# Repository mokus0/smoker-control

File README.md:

Smoker Command Center
======================

First, an up front warning:  I don't have nearly enough time for this project.  Feel free to use anything you want from this project, and if you run into issues I'd love to try to help - *if* I can find the time.  And that's a BIG "if".

Now that that's out of the way... This is the very beginning of a project that brings together two of my favorite hobbies, neither of which I do nearly enough of: electronics and cooking.  There's not much to see here yet, and there may never be, but what I'd *like* to make here is a weatherproof, wireless, battery powered (with solar charging) general-purpose sensor pod, rigged up with a bunch of useful sensors on my backyard smoker.

On the software side, I'd like to put together a sort of "big board", giving me a nice overview of the recent history of the sensors and some analysis of the data (rates of change of temperatures, estimated amount of fuel to add, estimated time to reach target temperatures, etc.).

For now, I've got a sensor measurement board design I'm working on.  It's primarily designed for precision resistance measurements across 5 decades, but useful for a lot of other analog sensors.

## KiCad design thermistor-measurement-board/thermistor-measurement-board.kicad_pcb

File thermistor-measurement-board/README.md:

Sensor front-end board
=======================

This board is an analog front-end designed to be able to interface with a very wide variety of sensors.  The immediate application is to read thermistors and RTDs, but it is massively overengineered for the task so it can be easily adapted to many other sensors.

The board provides 16 single-ended channels (or, depending how the board is stuffed, these 16 channels can be paired in any combination for differential measurement).  I haven't built the board yet but each input *should* have very high input impedance (around 2 GΩ on the high gain channel and 10 TΩ on the unity-gain channel), very low noise, very good linearity and (after ADC calibration) very good overall accuracy.  Up to 2 channels can be sampled simultaneously by a 24-bit ADC with programmable gain from 1 to 32 V/V, and the input amps are additionally configured for two different levels of gain (unity and 100x) to widen the range the board can handle.

Each channel can also be independently connected to one of two bias supplies, with very accurate on-board voltage and current references.

Pretty much every major component on the board other than the muxes is optional and can be bypassed to use the rest of the board in a useful way.

We shall see how the analog performance comes out; I've been working in a very limited space to keep prototyping costs down, but I've also been pretty careful with the layout so I'm optimistic.  I've managed to fit it on a 1.2" by 2" board using relatively large components (nothing smaller than 0402) so it should still be feasible to hand-assemble.  I've tried to keep things reasonably accessible for rework as well, but in some areas rework will be a challenge without very good tools.

Contents
=========

(most parts optional, see schematic for details): 

* MAX6070 voltage reference (x2)

* AD8277 dual difference amp and AD8607 dual op amp configured as two current sources (limited to relatively low output currents, intended for use as bias supplies for resistive sensors)

* MAX14661 multiplexer (x2): the first connects 2 power sources to 16 sensor channels and the other connects the same sensor channels to 2 sampling channels.  These are on separate pins to support 3-terminal measurements, and with a bit of finagling channels can be ganged together to support 4-terminal measurements.

* MAX4209 and MCP6N11 instrument amps to provide high impedance at the sensor measurement terminals and a couple gain ranges.

* MCP3911 24-bit ADC with analog front-end.  This is a very inexpensive part so I'm a bit concerned it may not perform as advertised, but I thought I'd give it a try.  On paper it's an interesting design, achieving very impressive specs for its price point through DSP techniques.

All parts except the current source have reasonably low active mode power consumption and very low power shutdown modes.  Current sources will pull around 250 µA each, but in practice I expect that for a full shutdown I'll cut power to the whole board.

Power supply info
==================

* MAX6070AAUT12+T (x2)

    Voltage:            2.7V - 5.5V (6V absolute max)
    
    Active current:     130 µA typical, 200 µA max
    
    Shutdown current:   6 µA max

* AD8277

    Voltage:            ±2V - ±18V (single or dual supply)
    
    Active current:     200 µA max (per channel?)
    
    Shutdown current:   N/A

* AD8607

    Voltage:            1.8V - 5V (6V absolute max)
    
    Active current:     40 µA typical, 50 µA max (per channel, x2)
    
    Shutdown current:   N/A

* MAX14661(x2)

    Voltage:            1.6V - 5.5V (6V absolute max)
    
    Active current:     675 µA typical, 1500 µA max
    
    Shutdown current:   1 µA max.

* MAX4209

    Voltage:            2.85V - 5.5V (6V absolute max)
    
    Active current:     1.4 mA typical, 2.3 mA max (using REFIN buffer)
    
    Shutdown current:   1.4 µA typical, 5 µA max.
    
    REFIN divider cur:  0.4 µA

* MCP6N11

    Voltage:            1.8V - 5.5V (6.5V absolute max)
    
    Active current:     800 µA typical, 1.1 mA max
    
    Shutdown current:   ~1 µA typical
    
    REF divider cur:    0.4 µA

* MCP3911

    Voltage:            2.7V - 3.6V (4V absolute max)
    
    Active current:     1.7 - 5.1 mA typical,
                        2.4 - ~7.5 mA max
                        (depending on configuration)
    
    Shutdown current:   2 µA max.

* Overall system (excluding dividers, leakage currents, etc)

    Voltage:            2.85V - 3.6V (4V absolute max)
    
    Active current:     ~10 mA max (lowest power ADC config)
    
    Shutdown current:   527 uA max (500 uA from the current sources).

Signal parameters, error analysis, etc
=======================================

* Voltage references

    When driving current source, will likely use 1.25V version.
    
    specs here are for "A" grade
    
    Initial accuracy ± 0.04%, max 6 ppm/ºC drift, 3.6 µV P-P noise (0.1 Hz to 10 kHz).
    200 mV dropout.
    Settling time after power-up or enable: 6 ms (or 60 µs if filter cap C208/C210 is removed)
    Very low output impedance (~ 0.1 Ω typically at 1 mA)

* Current sources

    These work by using a unity-gain difference amplifier to drive a set resistor (on the high side of a load) to a target voltage.  The second op-amp increases the input impedance of the feedback loop (without the op-amp, this would be 80 kΩ) to reduce error when driving high-impedance loads.
    
    Because of the feedback topology, all input voltages from GND to VS are valid as long as VS is at least 3V.  The output swing will range from GND (plus whatever offset is present at minimum load resistance) to VS - 0.2V - V_in at the low side of the sense resistor.
    
    difference amp (specs here are for "B" grade):
    
    system offset 200 µV max (0.012% with 1.25V reference)
    gain error 0.02% max (250 µV with 1.25V reference)
    differential input impedance 80 kΩ (about 1.25 ppm error on input from voltage ref's 0.1 Ω output)
    settling time to 0.001%: 16 µs max
    output noise 7 µV P-P max, 0.1 Hz - 10 kHz
    
    feedback buffer:
    
    offset error 50 µV max (0.004% with 1.25V reference)
    input bias current 1 pA max (1 µV error with 1 MΩ set resistor)
    output noise 3.5 µV P-P max, 0.1 Hz - 1 MHz
    
    total set-resistor voltage error (vref + diff amp + feedback buffer): 1 mV (0.08%).
    
    At these error levels, although the resistor error technically composes nonlinearly, the nonlinearity is negligible.  With a 0.02% set resistor, for xample, current accuracy should be 0.1% worst-case.  A 0.1% resistor should give 0.18% percent worst-case current accuracy.

* Bias mux

    This mux distributes bias current from either or both sources to any combination of the sensor channels.  The measurement is performed through a separate mux, to eliminate measurement errors due to the switch resistance of this mux.  If using a voltage-mode bias, the mux will add 8-12Ω (max) of fairly flat (24 mΩ, typically around 0.5%) source impedance, with channels typically matching to within 0.25Ω (around 5%).  Datasheet is not clear on whether these values are stable over time but I'd expect they are, and channels could be individually calibrated.
    
    input/output signal voltage range: ±5.5V
    ESD protection: ±10kV on all muxed pins
    switch on-state leakage current ±50 nA max (±5% error on 1 µA bias current).  This is with lines held at absolute limits: not sure what leakage would be at more typical voltages (≤0.6V), or how consistent it might be.  This figure definitely makes me worry about this mux.  To be fair, the graphs appear to show the "typical" figure to be a couple orders of magnitude lower, and very flat in all dimensions across ranges we care about.  I think I'm going to roll the dice on it - I have several options to work around it if it does turn out to be problematic (including the perfectly viable "screw it, let it be wrong at low bias currents" option, which won't harm my initial application for this board much).

* Sense mux

    This mux connects sensor channels to measurement channels.
    
    Same part as bias mux.

* MAX4208/9

    Not suitable for both channels; it's only designed for up to about ±100 mV differential mode.  Future iterations may use MCP6N11 for both channels as it seems well-suited to a wide gain range, but for now I want to try this one out for a high-gain channel as it has several features that make it appealing for high-gain small-signal applications.

    Input common-mode range (3V supply): -0.1V to 1.7V.  IN- will typically be GND so IN+ can swing rail-to-rail.
    Output voltage swings to within a few tens of mV of either rail.
    ADC input absolute max is only +2V though, so output channels are clamped to 1.8V by zener diodes (TODO: is there a better choice here?).  If amp tries to drive higher than 1.8V, it will source up to 20 mA (typical) through the zener diodes (and can do so continuously with no harm other than the wasted power), after which it will take about 0.5 ms to recover.
    
    Input differential mode range:
    datasheet recommends keeping below 100mV or linearity is poor.
    
    Input resistance 2 GΩ, bias current 1 pA (negligible error for 1 uA bias current)
    
    Input offset ±20 µV max
    Gain can be set for unity or higher.  Gain error at 100V/V with Vdiff ±20mV (doesn't say how accurate the set resistors were): ±0.25% max

* MCP6N11

    Input common-mode range (3V supply): -0.2V to 3.15V
    Common-mode non-linearity (non-linear change of input offset with common-mode voltage): 0.1% worst-case (unity gain, 1.8V supply) - typically much better
    Gain error ±1% max, but very low drift (6 ppm/ºC)
    Differential non-linearity
        (G = 1): ±30 ppm typical, ±500 ppm max
        (G = 10, 100): ±100 ppm typical, ±2000 ppm max
    
    Input bias current 10 pA typical, 5 nA max (at 125ºC)
    Input resistance 10TΩ
    
    Output voltage swing: within about 25 mV of rails
    Output impedance: (G = 1, 10) 900Ω typical (G = 100) 600Ω typical

* ADC

    This is a pretty interesting ADC architecture - it uses a 5-level sigma-delta frontend and DSP oversampling to achieve 24 bit resolution with fairly low noise and very good overall signal performance (if oversampling by a large enough factor).
    Biggest weakness is that it only tolerates ±2V input.
    
    Input absolute range: ±1V
    Input differential-mode range: ±0.6V full scale (divided by gain)
    Offset, gain error and vref tolerance are relatively high but can be calibrated fairly well (gain error drift is 1 ppm/ºC, INL is 5 ppm, internal vref TC is 7 ppm/ºC)

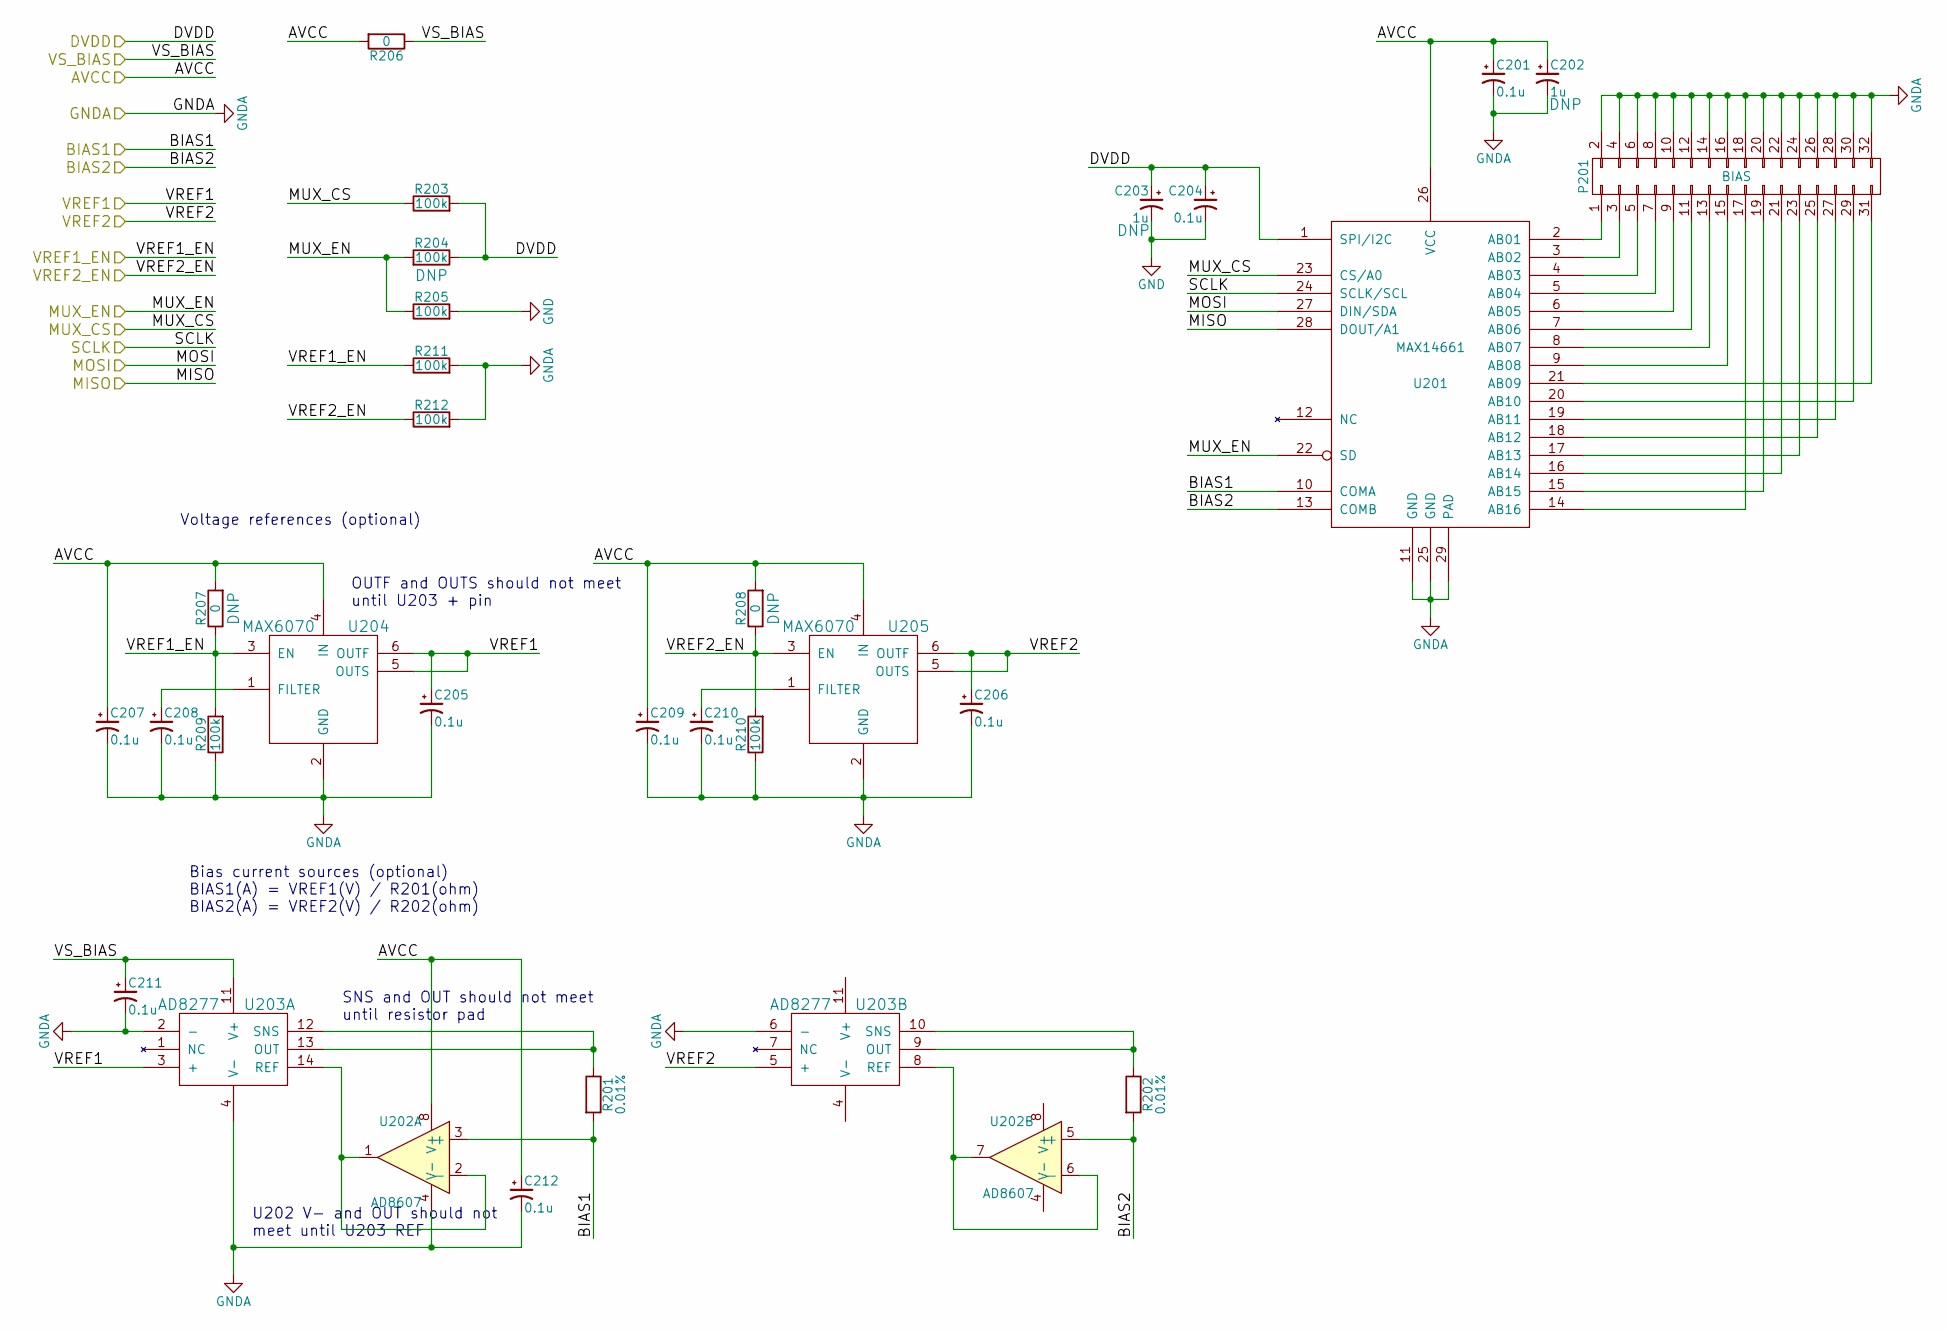
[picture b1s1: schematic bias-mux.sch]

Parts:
C201, C204, C205, C206, C207, C208, C209, C210, C211, C212: 0.1u; C_0402
C202, C203: 1u; C_0603
P201: BIAS; Pin_Header_Straight_2x16
R201, R202: 0.01%; R_0603
R203, R204, R205: 100k; R_0603
R206, R207, R208: 0; R_0402
R209, R210, R211, R212: 100k; R_0402
U201: MAX14661; Maxim_90-0035
U202: AD8607; MSOP-8_3x3mm_Pitch0.65mm
U203: AD8277; SOIC-14_3.9x8.7mm_Pitch1.27mm
U204, U205: MAX6070; Maxim_90-0175

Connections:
/ADC/AVCC: C201.1, C202.1, C207.1, C209.1, C212.1, R206.2, R207.2, R208.2, U201.26 (VCC), U202.8 (V+), U204.4 (IN), U205.4 (IN); also elsewhere on the board
/ADC/DVDD: C203.1, C204.1, R203.2, R204.1, U201.1 (SPI/I2C); also elsewhere on the board
/ADC/MISO: U201.28 (DOUT/A1); also elsewhere on the board
/ADC/MOSI: U201.27 (DIN/SDA); also elsewhere on the board
/ADC/SCLK: U201.24 (SCLK/SCL); also elsewhere on the board
/Bias/BIAS1: R201.2, U201.10 (COMA), U202.3 (+); also elsewhere on the board
/Bias/BIAS2: R202.2, U201.13 (COMB), U202.5 (+); also elsewhere on the board
/Bias/MUX_CS: R203.1, U201.23 (CS/A0); also elsewhere on the board
/Bias/MUX_EN: R204.2, R205.1, U201.22 (SD); also elsewhere on the board
/Bias/VREF1: C205.1, U203.3 (+), U204.5 (OUTS), U204.6 (OUTF); also elsewhere on the board
/Bias/VREF1_EN: R207.1, R209.2, R211.1, U204.3 (EN); also elsewhere on the board
/Bias/VREF2: C206.1, U203.5 (+), U205.5 (OUTS), U205.6 (OUTF); also elsewhere on the board
/Bias/VREF2_EN: R208.1, R210.2, R212.1, U205.3 (EN); also elsewhere on the board
/Bias/VS_BIAS: C211.1, R206.1, U203.11 (V+); also elsewhere on the board
GND: C203.2, C204.2, R205.2; also elsewhere on the board
GNDA: C201.2, C202.2, C205.2, C206.2, C207.2, C208.2, C209.2, C210.2, C211.2, C212.2, P201.2, P201.4, P201.6, P201.8, P201.10, P201.12, P201.14, P201.16, P201.18, P201.20, P201.22, P201.24, P201.26, P201.28, P201.30, P201.32, R209.1, R210.1, R211.2, R212.2, U201.11 (GND), U201.25 (GND), U201.29 (PAD), U202.4 (V-), U203.2 (-), U203.4 (V-), U203.6 (-), U204.2 (GND), U205.2 (GND); also elsewhere on the board
unnamed: C208.1, U204.1 (FILTER)
unnamed: C210.1, U205.1 (FILTER)
unnamed: P201.1, U201.2 (AB01)
unnamed: P201.3, U201.3 (AB02)
unnamed: P201.5, U201.4 (AB03)
unnamed: P201.7, U201.5 (AB04)
unnamed: P201.9, U201.6 (AB05)
unnamed: P201.11, U201.7 (AB06)
unnamed: P201.13, U201.8 (AB07)
unnamed: P201.15, U201.9 (AB08)
unnamed: P201.17, U201.14 (AB16)
unnamed: P201.19, U201.15 (AB15)
unnamed: P201.21, U201.16 (AB14)
unnamed: P201.23, U201.17 (AB13)
unnamed: P201.25, U201.18 (AB12)
unnamed: P201.27, U201.19 (AB11)
unnamed: P201.29, U201.20 (AB10)
unnamed: P201.31, U201.21 (AB09)
unnamed: R201.1, U203.12 (SNS), U203.13 (OUT)
unnamed: R202.1, U203.9 (OUT), U203.10 (SNS)
unnamed: U202.1, U202.2 (-), U203.14 (REF)
unnamed: U202.6 (-), U202.7, U203.8 (REF)

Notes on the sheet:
Bias current sources (optional) BIAS1(A) = VREF1(V) / R201(ohm) BIAS2(A) = VREF2(V) / R202(ohm)
SNS and OUT should not meet until resistor pad
OUTF and OUTS should not meet until U203 + pin
Voltage references (optional)
U202 V- and OUT should not meet until U203 REF

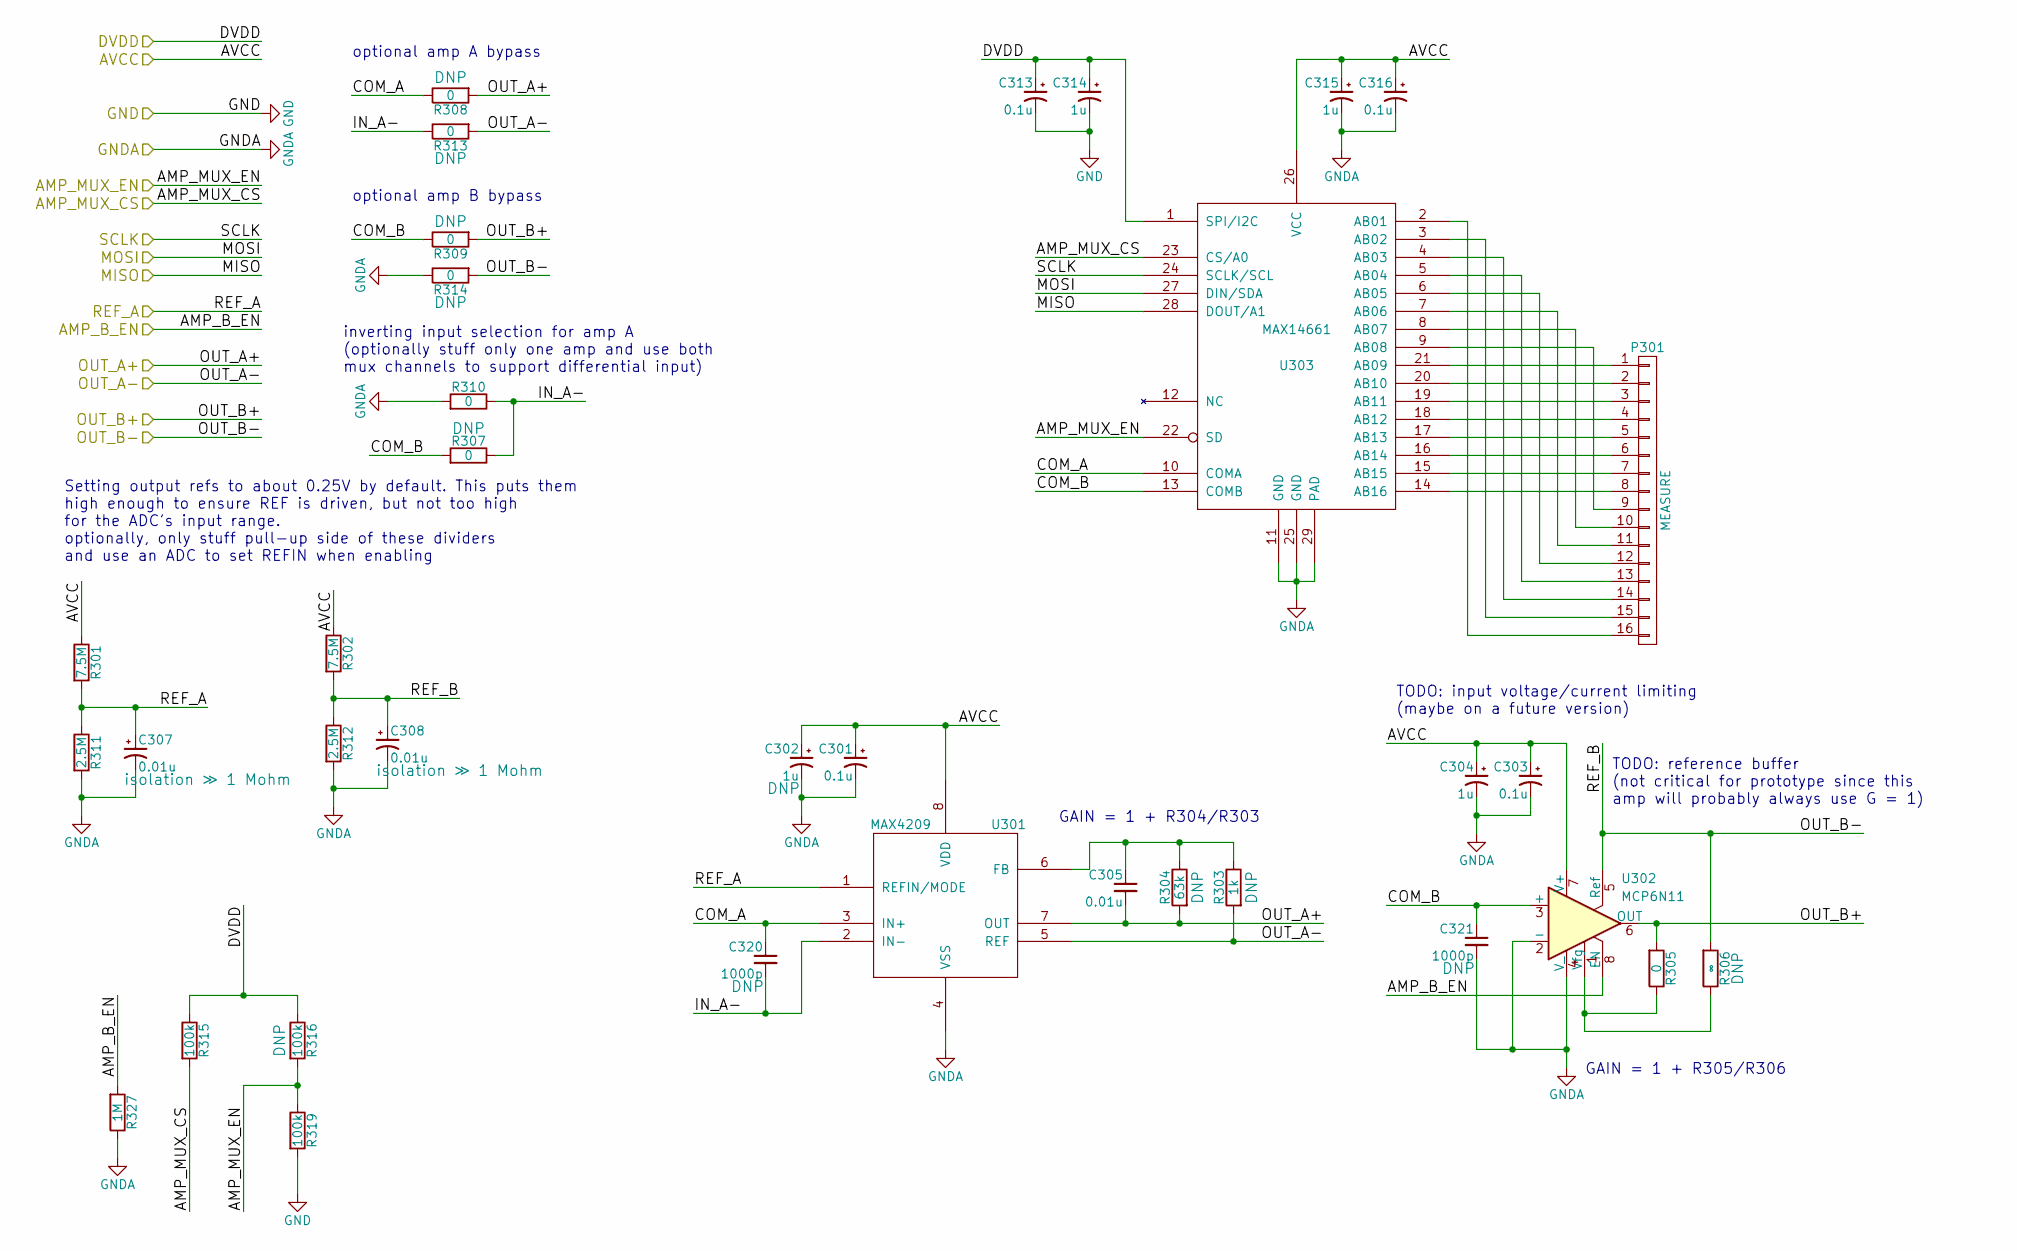
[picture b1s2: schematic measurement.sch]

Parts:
C301, C303, C313, C316: 0.1u; C_0402
C302, C304, C314, C315: 1u; C_0603
C305, C307, C308: 0.01u; C_0402
C320, C321: 1000p; C_0402
P301: MEASURE; Pin_Header_Straight_1x16
R301, R302: 7.5M; R_0402
R303: 1k; R_0402
R304: 63k; R_0402
R305, R307, R308, R310, R313: 0; R_0402
R306: ∞; R_0402
R309, R314: 0; R_0603
R311, R312: 2.5M; R_0402
R315, R316, R319: 100k; R_0603
R327: 1M; R_0603
U301: MAX4209; MSOP-8_3x3mm_Pitch0.65mm
U302: MCP6N11; SOIC-8_3.9x4.9mm_Pitch1.27mm
U303: MAX14661; Maxim_90-0035

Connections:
/ADC/AVCC: C301.1, C302.1, C303.1, C304.1, C315.1, C316.1, R301.1, R302.1, U301.8 (VDD), U302.7 (V+), U303.26 (VCC); also elsewhere on the board
/ADC/DVDD: C313.1, C314.1, R315.1, R316.1, U303.1 (SPI/I2C); also elsewhere on the board
/ADC/MISO: U303.28 (DOUT/A1); also elsewhere on the board
/ADC/MOSI: U303.27 (DIN/SDA); also elsewhere on the board
/ADC/OUT_A+: C305.2, R304.2, R308.2, U301.7 (OUT); also elsewhere on the board
/ADC/OUT_A-: R303.2, R313.2, U301.5 (REF); also elsewhere on the board
/ADC/OUT_B+: R305.2, R309.2, U302.6 (OUT); also elsewhere on the board
/ADC/OUT_B-: C308.1, R302.2, R306.2, R312.1, R314.2, U302.5 (Ref); also elsewhere on the board
/ADC/SCLK: U303.24 (SCLK/SCL); also elsewhere on the board
/Interface/AMP_MUX_CS: R315.2, U303.23 (CS/A0); also elsewhere on the board
/Interface/AMP_MUX_EN: R316.2, R319.1, U303.22 (SD); also elsewhere on the board
/Interface/REF_A: C307.1, R301.2, R311.1, U301.1 (REFIN/MODE); also elsewhere on the board
/Sensor input/AMP_B_EN: R327.2, U302.8 (EN); also elsewhere on the board
/Sensor input/COM_A: C320.1, R308.1, U301.3 (IN+), U303.10 (COMA)
/Sensor input/COM_B: C321.1, R307.2, R309.1, U302.3 (+), U303.13 (COMB)
/Sensor input/IN_A-: C320.2, R307.1, R310.1, R313.1, U301.2 (IN-)
GND: C313.2, C314.2, R319.2; also elsewhere on the board
GNDA: C301.2, C302.2, C303.2, C304.2, C307.2, C308.2, C315.2, C316.2, C321.2, R310.2, R311.2, R312.2, R314.1, R327.1, U301.4 (VSS), U302.2 (-), U302.4 (V_), U303.11 (GND), U303.25 (GND), U303.29 (PAD); also elsewhere on the board
unnamed: C305.1, R303.1, R304.1, U301.6 (FB)
unnamed: P301.1, U303.21 (AB09)
unnamed: P301.2, U303.20 (AB10)
unnamed: P301.3, U303.19 (AB11)
unnamed: P301.4, U303.18 (AB12)
unnamed: P301.5, U303.17 (AB13)
unnamed: P301.6, U303.16 (AB14)
unnamed: P301.7, U303.15 (AB15)
unnamed: P301.8, U303.14 (AB16)
unnamed: P301.9, U303.9 (AB08)
unnamed: P301.10, U303.8 (AB07)
unnamed: P301.11, U303.7 (AB06)
unnamed: P301.12, U303.6 (AB05)
unnamed: P301.13, U303.5 (AB04)
unnamed: P301.14, U303.4 (AB03)
unnamed: P301.15, U303.3 (AB02)
unnamed: P301.16, U303.2 (AB01)
unnamed: R305.1, R306.1, U302.1 (Vfg)

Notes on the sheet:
optional amp A bypass
GAIN = 1 + R304/R303
inverting input selection for amp A (optionally stuff only one amp and use both mux channels to support differential input)
Setting output refs to about 0.25V by default. This puts them high enough to ensure REF is driven, but not too high for the ADC's input range. optionally, only stuff pull-up side of these dividers and use an ADC to set REFIN when enabling
TODO: reference buffer (not critical for prototype since this amp will probably always use G = 1)
GAIN = 1 + R305/R306
optional amp B bypass
TODO: input voltage/current limiting (maybe on a future version)

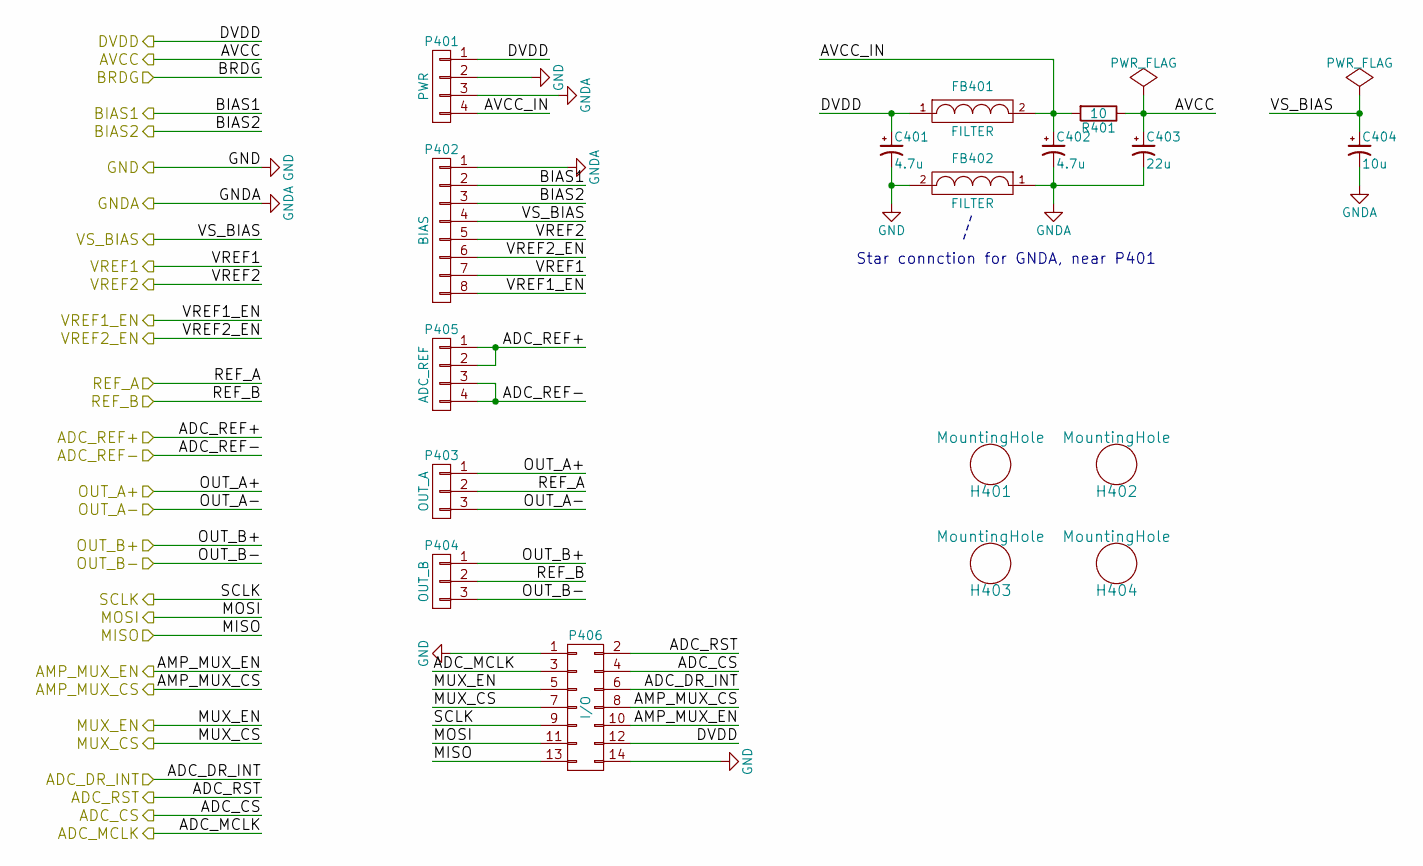
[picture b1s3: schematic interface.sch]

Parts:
C401, C402: 4.7u; C_1210
C403: 22u; C_1210
C404: 10u; C_1210
FB401, FB402: FILTER; R_1210; MFG part number FBMH3225HM202NT
H401, H402, H403, H404: MountingHole; MountingHole_2-5mm
P401: PWR; Pin_Header_Straight_1x04
P402: BIAS; Pin_Header_Straight_1x08
P403: OUT_A; Pin_Header_Straight_1x03
P404: OUT_B; Pin_Header_Straight_1x03
P405: ADC_REF; Pin_Header_Straight_1x04
P406: I/O; Pin_Header_Straight_2x07
R401: 10; R_1210

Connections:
/ADC/ADC_CS: P406.4; also elsewhere on the board
/ADC/ADC_DR_INT: P406.6; also elsewhere on the board
/ADC/ADC_MCLK: P406.3; also elsewhere on the board
/ADC/ADC_REF+: P405.1, P405.2; also elsewhere on the board
/ADC/ADC_REF-: P405.3, P405.4; also elsewhere on the board
/ADC/ADC_RST: P406.2; also elsewhere on the board
/ADC/AVCC: C403.1, R401.1; also elsewhere on the board
/ADC/DVDD: C401.1, FB401.1, P401.1, P406.12; also elsewhere on the board
/ADC/MISO: P406.13; also elsewhere on the board
/ADC/MOSI: P406.11; also elsewhere on the board
/ADC/OUT_A+: P403.1; also elsewhere on the board
/ADC/OUT_A-: P403.3; also elsewhere on the board
/ADC/OUT_B+: P404.1; also elsewhere on the board
/ADC/OUT_B-: P404.3; also elsewhere on the board
/ADC/SCLK: P406.9; also elsewhere on the board
/Bias/BIAS1: P402.2; also elsewhere on the board
/Bias/BIAS2: P402.3; also elsewhere on the board
/Bias/MUX_CS: P406.7; also elsewhere on the board
/Bias/MUX_EN: P406.5; also elsewhere on the board
/Bias/VREF1: P402.7; also elsewhere on the board
/Bias/VREF1_EN: P402.8; also elsewhere on the board
/Bias/VREF2: P402.5; also elsewhere on the board
/Bias/VREF2_EN: P402.6; also elsewhere on the board
/Bias/VS_BIAS: C404.1, P402.4; also elsewhere on the board
/Interface/AMP_MUX_CS: P406.8; also elsewhere on the board
/Interface/AMP_MUX_EN: P406.10; also elsewhere on the board
/Interface/AVCC_IN: C402.1, FB401.2, P401.4, R401.2
/Interface/REF_A: P403.2; also elsewhere on the board
/Sensor input/AMP_B_EN: P404.2; also elsewhere on the board
GND: C401.2, FB402.2, P401.2, P406.1, P406.14; also elsewhere on the board
GNDA: C402.2, C403.2, C404.2, FB402.1, P401.3, P402.1; also elsewhere on the board

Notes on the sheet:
Star connction for GNDA, near P401

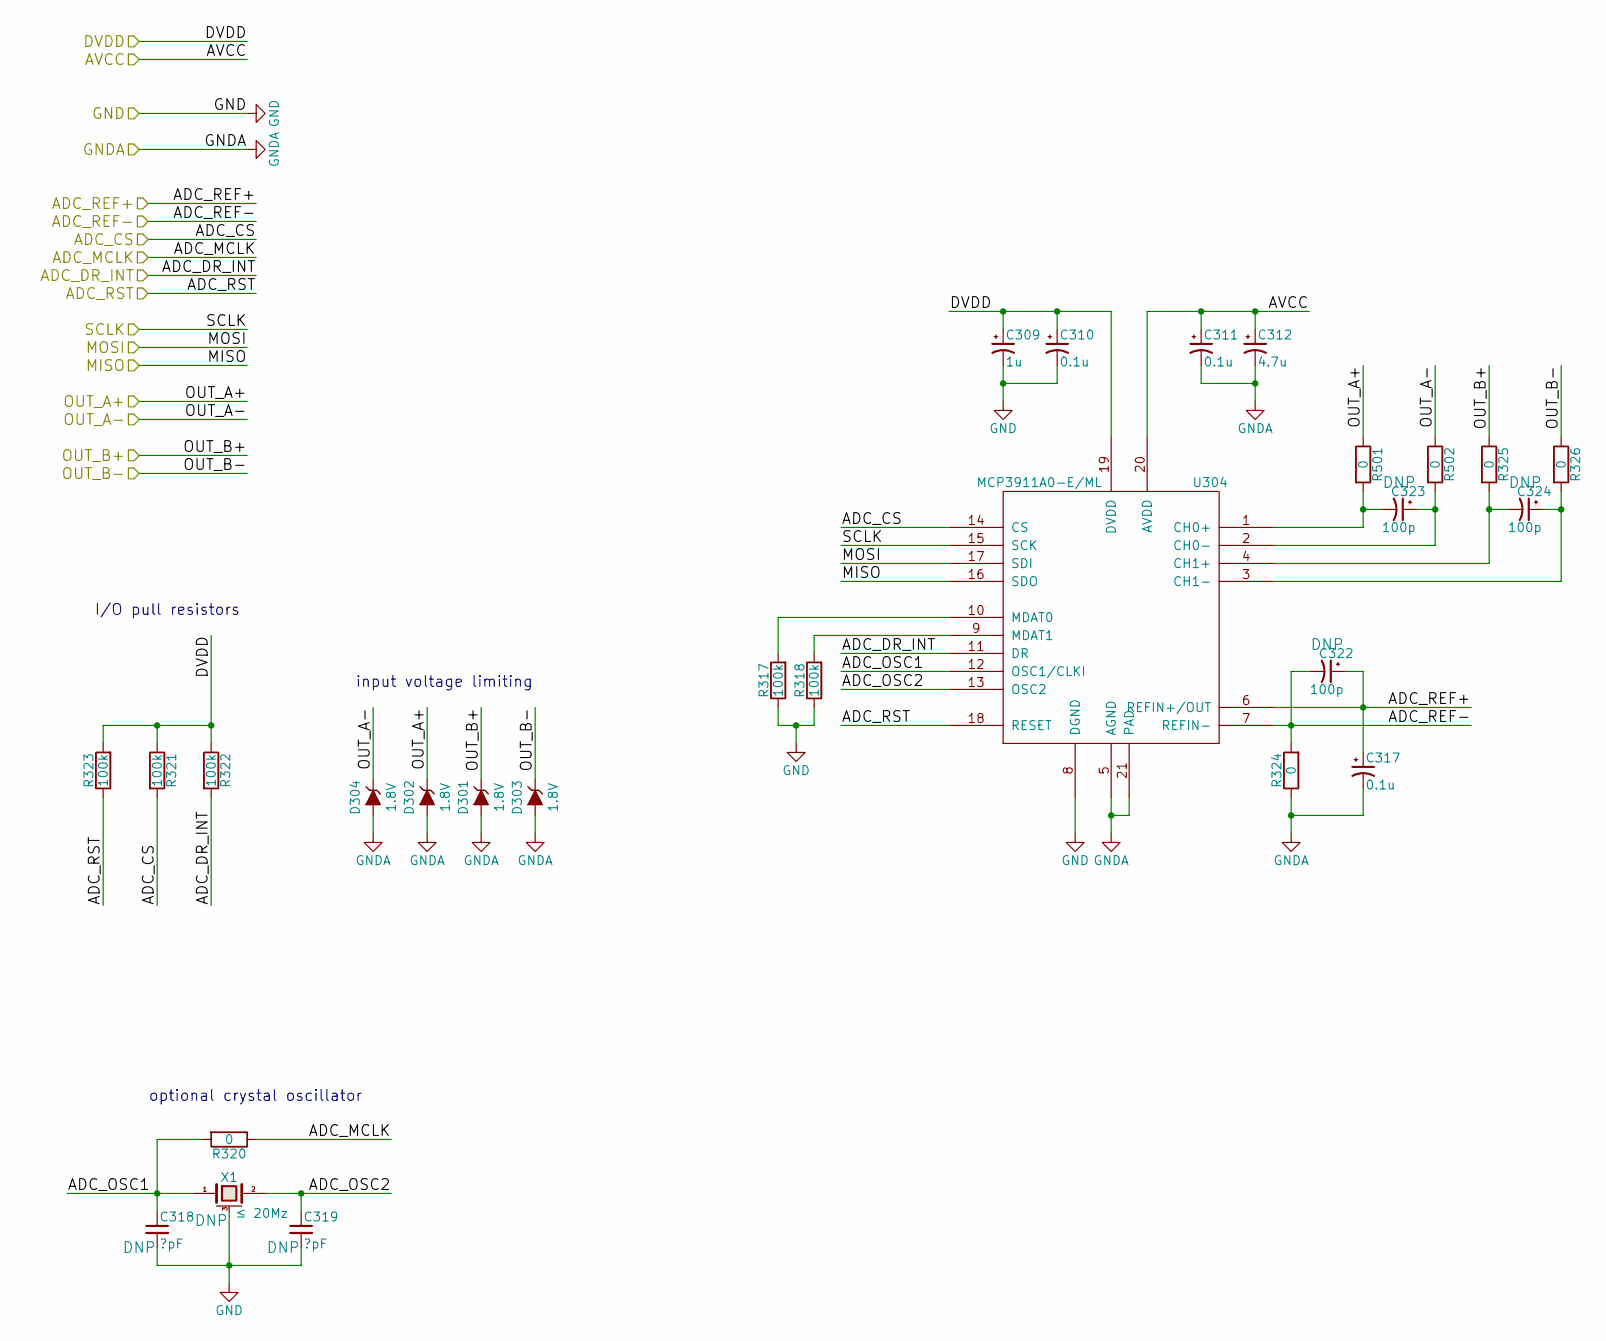
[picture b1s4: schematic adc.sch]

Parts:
C309: 1u; C_0603
C310, C311, C317: 0.1u; C_0402
C312: 4.7u; C_0805
C318, C319: ?pF; C_0402
C322, C323, C324: 100p; C_0402
D301, D302, D303, D304: 1.8V; SOD-123
R317, R318, R321, R322, R323: 100k; R_0603
R320, R324, R325, R326, R501, R502: 0; R_0603
U304: MCP3911A0-E/ML; QFN-20-1EP_4x4mm_Pitch0.5mm
X1: ≤ 20Mz; crystal_FA238-TSX3225

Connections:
/ADC/ADC_CS: R321.2, U304.14 (CS); also elsewhere on the board
/ADC/ADC_DR_INT: R322.2, U304.11 (DR); also elsewhere on the board
/ADC/ADC_MCLK: R320.1; also elsewhere on the board
/ADC/ADC_OSC1: C318.1, R320.2, U304.12 (OSC1/CLKI), X1.1
/ADC/ADC_OSC2: C319.1, U304.13 (OSC2), X1.2
/ADC/ADC_REF+: C317.1, C322.1, U304.6 (REFIN+/OUT); also elsewhere on the board
/ADC/ADC_REF-: C322.2, R324.2, U304.7 (REFIN-); also elsewhere on the board
/ADC/ADC_RST: R323.1, U304.18 (RESET); also elsewhere on the board
/ADC/AVCC: C311.1, C312.1, U304.20 (AVDD); also elsewhere on the board
/ADC/DVDD: C309.1, C310.1, R321.1, R322.1, R323.2, U304.19 (DVDD); also elsewhere on the board
/ADC/MISO: U304.16 (SDO); also elsewhere on the board
/ADC/MOSI: U304.17 (SDI); also elsewhere on the board
/ADC/OUT_A+: D302.1 (K), R501.1; also elsewhere on the board
/ADC/OUT_A-: D304.1 (K), R502.1; also elsewhere on the board
/ADC/OUT_B+: D301.1 (K), R325.1; also elsewhere on the board
/ADC/OUT_B-: D303.1 (K), R326.1; also elsewhere on the board
/ADC/SCLK: U304.15 (SCK); also elsewhere on the board
GND: C309.2, C310.2, C318.2, C319.2, R317.1, R318.1, U304.8 (DGND), X1.3 (case); also elsewhere on the board
GNDA: C311.2, C312.2, C317.2, D301.2 (A), D302.2 (A), D303.2 (A), D304.2 (A), R324.1, U304.5 (AGND), U304.21 (PAD); also elsewhere on the board
unnamed: C323.1, R502.2, U304.2 (CH0-)
unnamed: C323.2, R501.2, U304.1 (CH0+)
unnamed: C324.1, R326.2, U304.3 (CH1-)
unnamed: C324.2, R325.2, U304.4 (CH1+)
unnamed: R317.2, U304.10 (MDAT0)
unnamed: R318.2, U304.9 (MDAT1)

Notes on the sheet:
input voltage limiting
optional crystal oscillator
I/O pull resistors

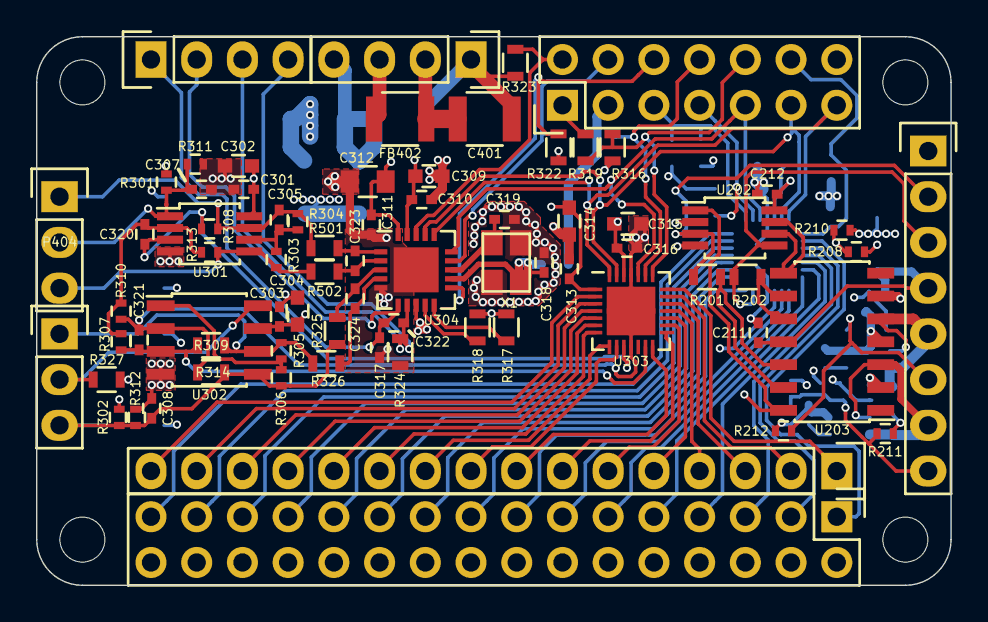
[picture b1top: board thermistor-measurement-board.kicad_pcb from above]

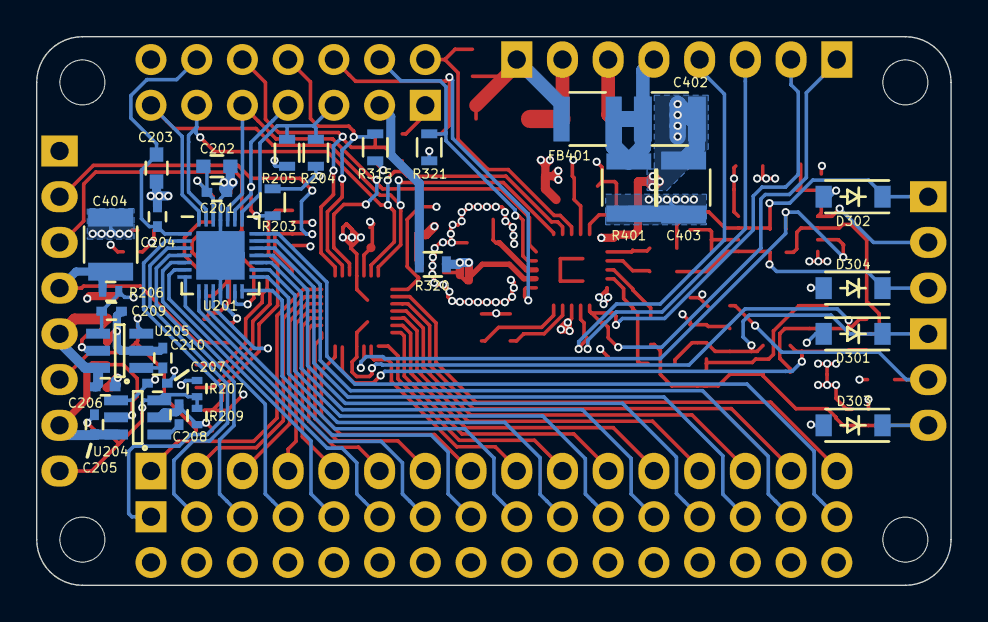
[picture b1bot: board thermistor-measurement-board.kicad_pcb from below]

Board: 4 copper layers, 50.8 x 30.5 mm, 109 parts (31 on the bottom side), 82 nets.

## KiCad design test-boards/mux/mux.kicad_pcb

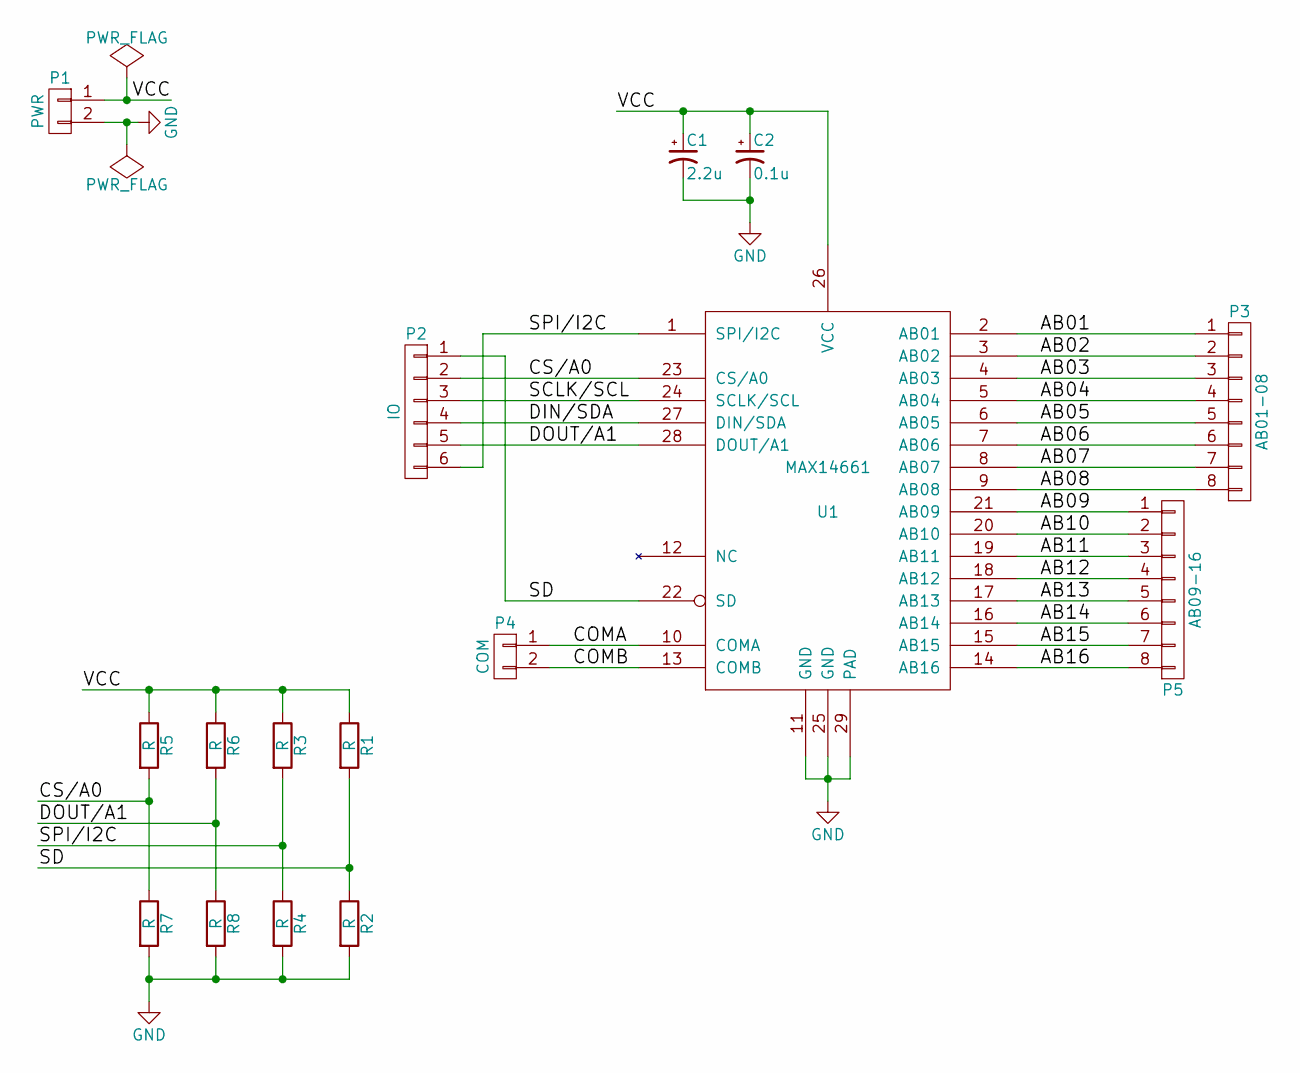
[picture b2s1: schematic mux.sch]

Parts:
C1: 2.2u; C_1210_HandSoldering
C2: 0.1u; C_0402
P1: PWR; Pin_Header_Straight_1x02
P2: IO; Pin_Header_Straight_1x06
P3: AB01-08; Pin_Header_Straight_1x08
P4: COM; Pin_Header_Straight_1x02
P5: AB09-16; Pin_Header_Straight_1x08
R1, R2, R3, R5, R6, R7, R8: R; R_0603_HandSoldering
R4: R; R_0402
U1: MAX14661; Maxim_90-0035

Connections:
/AB01: P3.1, U1.2 (AB01)
/AB02: P3.2, U1.3 (AB02)
/AB03: P3.3, U1.4 (AB03)
/AB04: P3.4, U1.5 (AB04)
/AB05: P3.5, U1.6 (AB05)
/AB06: P3.6, U1.7 (AB06)
/AB07: P3.7, U1.8 (AB07)
/AB08: P3.8, U1.9 (AB08)
/AB09: P5.1, U1.21 (AB09)
/AB10: P5.2, U1.20 (AB10)
/AB11: P5.3, U1.19 (AB11)
/AB12: P5.4, U1.18 (AB12)
/AB13: P5.5, U1.17 (AB13)
/AB14: P5.6, U1.16 (AB14)
/AB15: P5.7, U1.15 (AB15)
/AB16: P5.8, U1.14 (AB16)
/COMA: P4.1, U1.10 (COMA)
/COMB: P4.2, U1.13 (COMB)
/CS/A0: P2.2, R5.2, R7.1, U1.23 (CS/A0)
/DIN/SDA: P2.4, U1.27 (DIN/SDA)
/DOUT/A1: P2.5, R6.2, R8.1, U1.28 (DOUT/A1)
/SCLK/SCL: P2.3, U1.24 (SCLK/SCL)
/SD: P2.1, R1.2, R2.1, U1.22 (SD)
/SPI/I2C: P2.6, R3.2, R4.1, U1.1 (SPI/I2C)
/VCC: C1.1, C2.1, P1.1, R1.1, R3.1, R5.1, R6.1, U1.26 (VCC)
GND: C1.2, C2.2, P1.2, R2.2, R4.2, R7.2, R8.2, U1.11 (GND), U1.25 (GND), U1.29 (PAD)

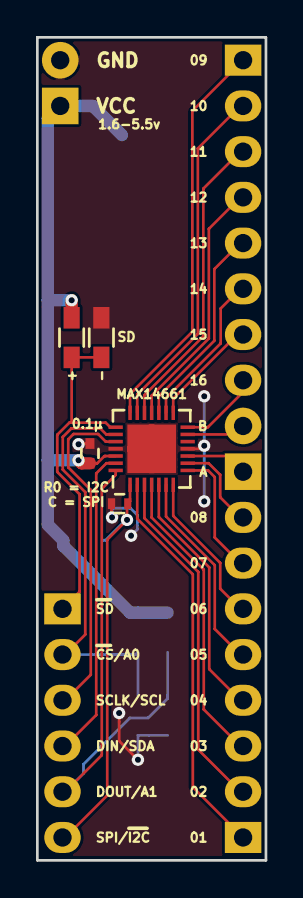
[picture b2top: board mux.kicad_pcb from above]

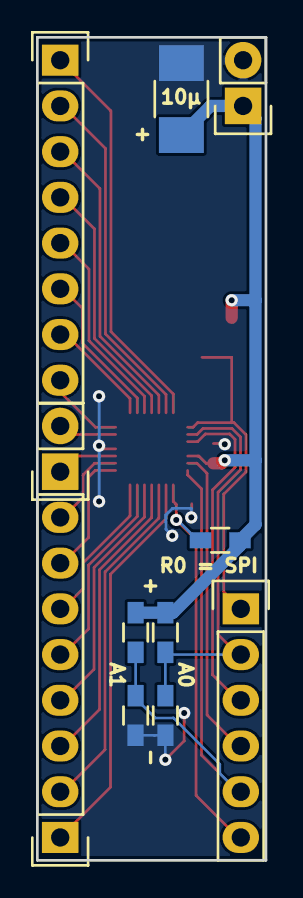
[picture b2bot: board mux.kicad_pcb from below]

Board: 2 copper layers, 12.7 x 45.7 mm, 16 parts (11 on the bottom side), 26 nets.

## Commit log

2016-02-10 initial import
2016-02-10 This project is in the public domain
2016-02-10 some schematic review and a new TODO list
2016-02-11 extracted board-specific info from main README into a new one in the board subdir
2016-02-11 took care of a few board review tasks
2016-02-11 added schematic pdf
2016-02-11 reviewed footprints
    they were all more or less correct, but i massaged a couple to closer match Maxim's recommended land patterns
2016-02-11 some notes and minor fiddling around
2016-02-11 experimenting with markdown formatting
2016-02-12 lots of design review and related fixes/improvements
2016-02-13 read a million instrument amp datasheets and found one that should work nicely for low gain.
2016-02-14 reviewed new inamp schematic
2016-03-10 added a breakout board for testing just the mux
2016-03-10 a few minor tweaks to thermistor board
